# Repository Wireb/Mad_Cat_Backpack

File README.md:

# Mad Cat Backpack
The Mad Cat Backpack is a animation upgrade for Mr TwinkleTwinkie's Mad Cat SAOs.
 
License is MIT so do what you want with it just don't litigate me. 

Current firmware runs a loop that waits a random amount of time between 0 and 8 minutes then picks a random animation. 

Current animations:
1. classic fade out fade in (random off delay)
2. blink / wink (random length random eye (left, right, or both) 
3. lip lick rights
4. lip lick left
5. piano teeth (random number of loops) 
6. eye bobble (random number of loops)
7. talking (random number of loops) 
8. sparkles (all random) 

Animations are NOT weighted evenly. Blinking has a higher probability then the others while sparkles has the least. 

Total code space use is ~36% so plenty of space for more animations if wanted. 

**NOTE** 
- When running off 5V power the LEDs are borderline too bright. Replace the 200 ohm resistors with a larger value to reduce brightness.

## KiCad
This is a KiCad 5.0 project. 
PCBs are also posed on OSHpark here: https://www.oshpark.com/shared_projects/GfiURq3q

## MplabX
This is a mplabX 5.05 project. All programming / debug was done with a PicKit4.
The firmware source is all contained in mad_cat_backpack_v0.asm 
If you just want to program a backpack using mad_cat_backpack.X.production.hex in microchip IPE is the fastest way. 

## Documentation
There is not much for documentation on this one. 

First you need a Mad Cat SAO from Mr TwinkleTwinkie:
- https://www.tindie.com/products/twinkletwinkie/twinkletwinkies-badgelife-sao-add-on-4/
- https://hackaday.io/project/159523-mad-cat

Next you need a backpack PCB:
- https://www.oshpark.com/shared_projects/GfiURq3q

Parts list for the backpack are:
 - 1x PIC16F1503-I/SL https://www.digikey.com/product-detail/en/microchip-technology/PIC16F1503-I-SL/PIC16F1503-I-SL-ND/2772041
 - 1x 10uF 10V or greater 0805 ceramic cap https://www.digikey.com/product-detail/en/samsung-electro-mechanics/CL21A106KPFNNNG/1276-6456-1-ND/5958084
 - 8x 200 ohm 0805 resistors (see note above about brightness) https://www.digikey.com/product-detail/en/yageo/AC0805JR-07200RL/YAG3769CT-ND/6006618
 - Optional 1x UJ2-MBH-1-SMT-TR mini USB jack https://www.digikey.com/product-detail/en/cui-inc/UJ2-MBH-1-SMT-TR/102-4003-1-ND/6187925
 - 8x white LEDs (reused the ones from the Mad Cat kit) 

 Assemble the back pack first. I just used a iron and tweezers to assemble mine. The LED pads ARE oversized to match the footprints on the Mad Cat. Center the LED between the pads and bridge the solder over to the terminals. Make sure the solder bridges are not taller thant the body of the LED. 

 Load the firmware using the 5 pads in the center of the board. The square pin is pin 1. 

 Test the backpack by plugging in power or USB. THe smile should dim in first then the eyes if so all is working and ready for final assembly. 

 Before final assembly the Mad Cat PCB needs to be modified. Look at Mad_Cat_modifications.jpg Cut the 4 traces marked by a red line. Make sure they are fully open. 

 Line up the backpack on the Mad Cat PCB. I used a 4 pin header though both sets of SAO holes then visually lined up the D3 and D8 leds with the solder mask holes in the Mad Cat PCB. 

 Once everything is lined up solder the 4 pads marked in blue boxes on Mad_Cat_modifications.jpg between the Mad Cat and the backpack. To do this I used a fine point soldering iron tip and some 0.5mm diameter solder. There is just enough space to get under the edge and heat the pads and the 0.5mm solder is small enough to slide between the two boards. 

 Final option step is to add yarn between the LEDs to prevent light leakage. I used some dark colored yarn and dental threaders to thread sections between all the LEDs. When in place cut the ends of the yarn off ass close to the backpack as possible and tuck the excess under the backpack. I also wrapped a piece of yarn around the edge of the backpack to keep light from spilling out behind the Mad Cat SAO.

Copyright (c) 2018 Peter Shabino

Permission is hereby granted, free of charge, to any person obtaining a copy of this hardware, software, and associated documentation files 
(the "Product"), to deal in the Product without restriction, including without limitation the rights to use, copy, modify, merge, publish, 
distribute, sublicense, and/or sell copies of the Product, and to permit persons to whom the Product is furnished to do so, subject to the 
following conditions:

The above copyright notice and this permission notice shall be included in all copies or substantial portions of the Product.

THE PRODUCT IS PROVIDED "AS IS", WITHOUT WARRANTY OF ANY KIND, EXPRESS OR IMPLIED, INCLUDING BUT NOT LIMITED TO THE WARRANTIES OF 
MERCHANTABILITY, FITNESS FOR A PARTICULAR PURPOSE AND NONINFRINGEMENT. IN NO EVENT SHALL THE AUTHORS OR COPYRIGHT HOLDERS BE LIABLE 
FOR ANY CLAIM, DAMAGES OR OTHER LIABILITY, WHETHER IN AN ACTION OF CONTRACT, TORT OR OTHERWISE, ARISING FROM, OUT OF OR IN CONNECTION 
WITH THE PRODUCT OR THE USE OR OTHER DEALINGS IN THE PRODUCT.

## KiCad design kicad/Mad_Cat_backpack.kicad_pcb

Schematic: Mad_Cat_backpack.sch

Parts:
C1: 10uF; C_0805
D1, D2, D3, D4, D5, D6, D7, D8: LED; LED_OSRAM_TOPLED_LxT776
J1: USB_B_Mini; USB_Mini_B_Female_UJ2-MBH-1-SMT-TR
J2: PicKit; Pin_Header_Straight_1x05_Pitch2.54mm
R1, R2, R3, R4, R5, R6, R7, R8: 200; R_0805_HandSoldering
U1: PIC16F1503; SOIC-14_3.9x8.7mm_Pitch1.27mm
X1: Badgelife_shitty_connector; Badgelife-Shitty-2x2
icon1: Metroid; metroid

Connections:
+5V: C1.1, J1.1 (VBUS), J2.2, R1.1, R2.1, R3.1, R4.1, R5.1, R6.1, R7.1, R8.1, U1.1, X1.1
GND: C1.2, J1.5 (GND), J1.6 (Shield), J2.3, U1.14, X1.2
unnamed: D1.1, U1.2
unnamed: D1.2, R2.2
unnamed: D2.1, U1.7
unnamed: D2.2, R3.2
unnamed: D3.1, U1.3
unnamed: D3.2, R1.2
unnamed: D4.1, U1.10
unnamed: D4.2, R8.2
unnamed: D5.1, U1.9
unnamed: D5.2, R7.2
unnamed: D6.1, U1.8
unnamed: D6.2, R6.2
unnamed: D7.1, U1.5
unnamed: D7.2, R5.2
unnamed: D8.1, U1.6
unnamed: D8.2, R4.2
unnamed: J2.1, U1.4
unnamed: J2.4, U1.13
unnamed: J2.5, U1.12

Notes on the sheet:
Copyright (c) 2018 Peter Shabino Permission is hereby granted, free of charge, to any person obtaining a copy of this hardware, software, and associated documentation files (the "Product"), to deal in the Product without restriction, including without limitation the rights to use, copy, modify, mer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

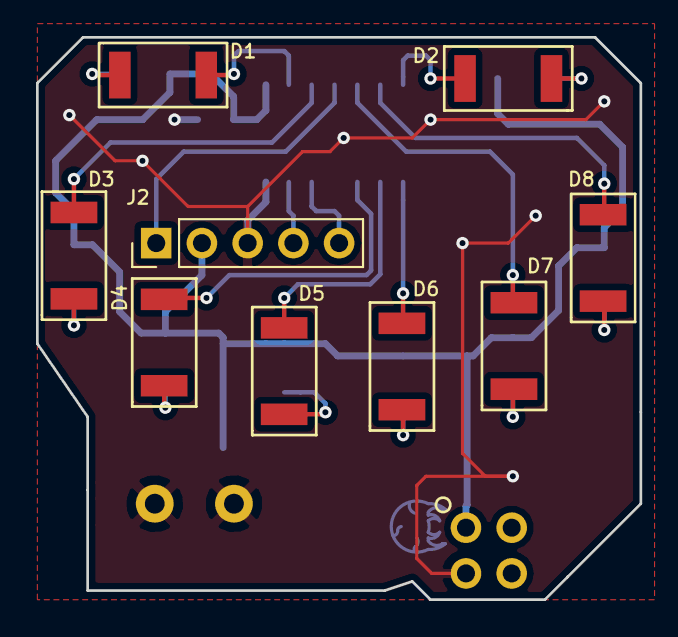
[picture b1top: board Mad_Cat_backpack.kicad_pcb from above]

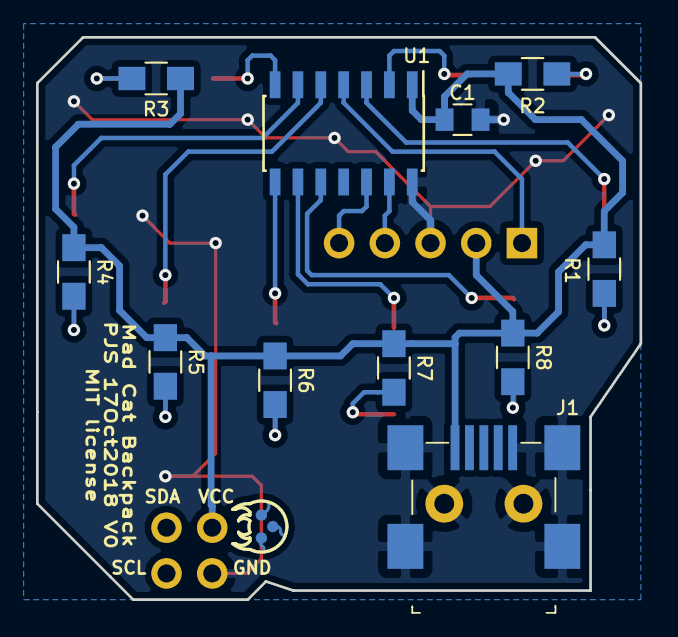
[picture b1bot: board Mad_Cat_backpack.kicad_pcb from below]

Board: 2 copper layers, 33.5 x 31.2 mm, 22 parts (12 on the bottom side), 21 nets.

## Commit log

2018-11-10 :circus_tent: Added .gitattributes & .gitignore files
2018-11-10 First push
2018-11-10 Documentation updates
2018-11-10 something

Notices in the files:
kicad/Mad_Cat_backpack.kicad_pcb:
MIT license
